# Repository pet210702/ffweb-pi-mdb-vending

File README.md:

# FF Getränkeautomat – MDB- & FFWEB-Steuerung für den SandenVendo G-Drink DM9

Open-Source-Steuerung auf Basis eines Raspberry Pi, die einen **SandenVendo G-Drink DM9** (über den **MDB-Cashless-Bus**), einen **13,56-MHz-USB-RFID-Leser**, ein **0,96"-I2C-OLED-Display**, **3 Bedientasten** und **FFWEB (`https://www.ffweb.at`)** zur Getränkeverrechnung im Feuerwehrhaus miteinander verbindet.

Läuft zuverlässig selbst auf einem einkernigen **Raspberry Pi 1 Model B+ (ARMv6, 512 MB RAM)** sowie auf neueren Modellen (Pi Zero 2 W, Pi 3, Pi 4, Pi 5).

---

## ✨ Funktionen

- **Zwei Bedienabläufe – „Chip zuerst“ und „Getränk zuerst“:**
  - *Chip zuerst:* Feuerwehr-Chip vorhalten → zwischen privatem Guthaben oder einer offenen Verrechnungsliste wählen → Kredit wird am G-Drink DM9 freigegeben → Getränk am Automaten wählen.
  - *Getränk zuerst:* Fach am G-Drink DM9 wählen → das OLED zeigt `Chip vorhalten` mit Getränkename und Preis → Chip vorhalten, die Ausgabe erfolgt sofort.
- **Verrechnungslisten / Anlässe:**
  - Offene Listen für Einsätze, Übungen oder Kameradschaftsabende / Sitzungen direkt im Web-Dashboard anlegen.
  - Sind Listen offen, wählen Mitglieder mit den **3 Tasten** (`Zurück`, `OK`, `Weiter`) zwischen **Privat (Guthaben)** und einer aktiven **Verrechnungsliste** (`0,00 EUR` privat, Buchung auf den Anlass).
- **Sichere Abrechnung – kein Abzug bei Störung oder Abbruch:**
  - Durchgehend Ganzzahl-Arithmetik in Cent.
  - Abgebucht wird **erst**, wenn der optische Ausgabesensor des DM9 `c,VEND,SUCCESS` meldet. Steckengebliebene Flaschen (`c,ERR,VEND 3`) oder abgebrochene Auswahlen (`c,ERR,VEND 1`) kosten `0,00 EUR`.
- **Offline-fähige SQLite-Warteschlange & idempotente FFWEB-Synchronisation:**
  - Jeder Verkauf wird sofort lokal in SQLite (`WAL`-Modus) mit eindeutigem `idempotency_key` (UUID) gespeichert.
  - Ist das WLAN/LAN oder FFWEB vorübergehend nicht erreichbar, überträgt ein Hintergrunddienst offene Buchungen automatisch nach – ohne Doppelbuchungen.
- **0,96"-OLED-Statusanzeige & Hardware-Überwachung:**
  - 4-zeilige Anzeige (`SSD1306` / `SH1106`, `128×64`) mit Bildschirmschoner, Boot-Splash und automatischer Textanpassung.
  - **OLED-Hot-Plug:** Wird das Display kurz getrennt oder verliert es die Versorgung, verbindet es sich automatisch neu und wird ohne Flackern neu initialisiert.
  - **RFID-Überwachung:** Wird der USB-Leser abgesteckt, erscheint sofort `FEHLER: RFID / Lesegerät getrennt / USB prüfen!`; nach dem Wiederanstecken läuft alles innerhalb von ca. 1,5 s weiter.
  - **Diagnose-Kombination (Taste 1 + 3):** Gleichzeitiges Drücken der linken und rechten Taste zeigt 10 Sekunden lang LAN-IP, MDB-Status, RFID-Status und die Anzahl offener Synchronisationen.
- **Web-Dashboard & virtueller G-Drink-DM9-Simulator (`/`):**
  - Fachbelegung, Test-Chips und Verrechnungslisten verwalten sowie den Live-Zustand der Hardware per Server-Sent Events (SSE) verfolgen.
  - Vollständiger Browser-Simulator für DM9, RFID-Leser, 3 Tasten und einen 128×64-OLED-Spiegel – alles lässt sich testen, bevor echte MDB-Hardware angeschlossen ist.

---

## 🛒 Stückliste

| Komponente | Empfohlenes Modell / Spezifikation | Schnittstelle | Hinweise |
| :--- | :--- | :--- | :--- |
| **Einplatinenrechner** | Raspberry Pi 1 Model B+ Rev 1.2 (oder Pi 3B+ / 4B / Zero 2 W) | Ethernet / USB / 40-Pin-GPIO | Debian Trixie / Raspberry Pi OS (32 oder 64 Bit) |
| **Kühlung (empfohlen beim Pi 1)** | 5-V-Alu-Kühlkörper + Lüfter + Kupfer-Shim (`15×15 mm`) | 5 V & GND (GPIO) | Ermöglicht stabilen 1000-MHz-Turbo bei ca. 30 °C |
| **MDB-Cashless-Interface** | **Qibixx MDB-USB Interface** (oder Qibixx MDB Pi HAT) | USB-CDC seriell (`/dev/ttyACM0`) | Verbindet den Pi mit dem 6-poligen Molex-MDB-Bus des Automaten |
| **RFID-Leser** | **13,56-MHz-USB-HID-Leser** (z. B. `Sycreader` / `IC_Reader 08ff:0009`) | USB-HID (`evdev`) | Liefert eine 10-stellige dezimale UID von MIFARE-Classic-/NFC-Chips |
| **OLED-Display** | **0,96"-I2C-OLED (`128×64`)** (`SSD1306` oder `SH1106`) | I2C (`/dev/i2c-1`, `0x3C`) | 4-polig (`VCC`, `GND`, `SCL`, `SDA`) |
| **Bedientasten (3×)** | Taster (6-mm-Printtaster oder 12/16-mm-Einbautaster) | GPIO + GND (Active-Low) | Nutzt die internen Pull-ups des Pi – keine externen Widerstände nötig |
| **Frontplatine (optional)** | [Eigene Frontplatine](#-frontplatine-oled--3-tasten) mit OLED + 3 Tastern | 7-polig JST-XH / Stiftleiste | Siehe [`hardware/front_panel_pcb`](hardware/front_panel_pcb/) |
| **Netzteil & Speicher** | Offizielles 5-V-Netzteil + 16-GB-Industrie-microSD | Strom / SD | High-Endurance-microSD für Dauerbetrieb empfohlen |
| **Getränkeautomat** | **SandenVendo G-Drink DM9** (mit SF01-Steuerplatine) | MDB-Slave | Lift-Automat für Flaschen/Dosen |

---

## 🔌 Verdrahtung (40-Pin-GPIO-Leiste des Raspberry Pi)

Alle Komponenten werden direkt an die GPIO-Leiste angeschlossen – ein zusätzlicher HAT ist nicht nötig:

```text
                 Raspberry Pi 40-Pin-GPIO-Leiste (Pins 1–20)
                 ┌──────────────────────┬──────────────────────┐
   OLED VCC  <── │ (01) 3,3 V           │ (02) 5 V             │──> Lüfter + (rot)
   OLED SDA  <── │ (03) GPIO 2 (SDA1)   │ (04) 5 V             │
   OLED SCL  <── │ (05) GPIO 3 (SCL1)   │ (06) GND             │──> Lüfter – (schwarz)
                 │ (07) GPIO 4          │ (08) GPIO 14 (TXD)   │
   OLED GND  <── │ (09) GND             │ (10) GPIO 15 (RXD)   │
   Taste 1   <── │ (11) GPIO 17         │ (12) GPIO 18         │
   Taste 2   <── │ (13) GPIO 27         │ (14) GND             │──> GND Taste 1 & 2
   Taste 3   <── │ (15) GPIO 22         │ (16) GPIO 23         │
                 │ (17) 3,3 V           │ (18) GPIO 24         │
                 │ (19) GPIO 10 (MOSI)  │ (20) GND             │──> GND Taste 3
                 └──────────────────────┴──────────────────────┘
```

### 1. 0,96"-I2C-OLED (`SSD1306` @ `0x3C`)
| OLED-Pin | Physischer Pin am Pi | GPIO / Funktion |
| :--- | :--- | :--- |
| **VCC** | **Pin 1** | `3,3 V` |
| **GND** | **Pin 9** | `GND` |
| **SDA** | **Pin 3** | `GPIO 2 (I2C1 SDA)` |
| **SCL** | **Pin 5** | `GPIO 3 (I2C1 SCL)` |

### 2. Drei Bedientasten (Active-Low mit internem Pull-up)
Jeder Taster hat zwei Anschlüsse: einer an den **GPIO-Pin**, der andere an einen beliebigen **GND-Pin** (Pins `14` und `20` liegen direkt gegenüber; alternativ eine gemeinsame Masseleitung durchschleifen).

| Position | Funktion | GPIO (BCM) | Physischer Pin | GND-Pin |
| :--- | :--- | :--- | :--- | :--- |
| **Taste 1 (links)** | **Zurück / Abbruch** | `GPIO 17` | **Pin 11** | **Pin 14** |
| **Taste 2 (Mitte)** | **Auswahl / OK** | `GPIO 27` | **Pin 13** | **Pin 14** |
| **Taste 3 (rechts)** | **Weiter ▶** | `GPIO 22` | **Pin 15** | **Pin 20** |

> **Tipp:** Im Ruhezustand (`IDLE`) **Taste 1 + Taste 3** gleichzeitig drücken, um das **10-Sekunden-Diagnosemenü** auf dem OLED anzuzeigen.

### 3. 5-V-Lüfter
| Lüfterkabel | Physischer Pin am Pi | Funktion |
| :--- | :--- | :--- |
| **Rot (+5 V)** | **Pin 2** oder **Pin 4** | `5 V` |
| **Schwarz (GND)** | **Pin 6** | `GND` |

### 4. USB-Geräte
- **USB-Port 1:** 13,56-MHz-USB-HID-RFID-Leser (`/dev/input/by-id/usb-...-event-kbd`).
- **USB-Port 2:** Qibixx MDB-USB Interface (`/dev/ttyACM0`), über den MDB-Kabelbaum mit dem G-Drink DM9 verbunden.

---

## 🟩 Frontplatine (OLED + 3 Tasten)

Für einen sauberen Einbau in die Automatentür gibt es eine eigene 2-lagige Frontplatine (`60 × 56 mm`, KiCad 9):

- **Vorderseite:** nur das 0,96"-OLED und die 3 Taster (`Zurück`, `OK`, `Weiter`) – keine sichtbaren Kabel.
- **Rückseite:** 7-poliger JST-XH-Stecker (`J1`) bzw. alternativ 7-polige 2,54-mm-Stiftleiste (`J2`) sowie der 100-nF-Abblockkondensator.
- Die 7 Signale (`+3V3`, `SDA`, `SCL`, `GND`, 3× Taster) passen direkt auf die Pins 1–15 der linken Reihe der GPIO-Leiste – exakt nach der Belegung oben.
- Fertige Gerber-Daten, BOM, Bestückungsdaten (JLCPCB) und ein STEP-Modell liegen in [`hardware/front_panel_pcb/production/`](hardware/front_panel_pcb/production/).

Details zu Pinbelegung, Abmessungen und Stückliste: [`hardware/front_panel_pcb/README.md`](hardware/front_panel_pcb/README.md).

---

## ⚙️ Hinweis zum RFID-UID-Format (USB-Leser vs. Smartphone-App)

Normale 13,56-MHz-MIFARE-Classic-Chips haben eine 4 Byte lange Seriennummer.
- **Smartphone-Apps (z. B. NFC Tools):** zeigen die Bytes in MSB-Reihenfolge (`04:A2:F3:9B`).
- **USB-Leser (10-stellige Dezimalausgabe):** drehen die 4 Bytes um (LSB zuerst: `9B F3 A2 04`) und geben den 32-Bit-Wert als 10-stellige Dezimalzahl mit führenden Nullen aus (`2616435204`).
- Mit dem **Live-Chip-Scanner** im Web-Dashboard (`http://<pi-ip>:8000`) sieht man die exakte UID des USB-Lesers und kann sie mit einem Klick kopieren.

---

## 🚀 Schnellstart (lokale Entwicklung & Simulator unter macOS / Linux)

Das komplette System läuft auch ohne angeschlossene Hardware mit dem eingebauten Simulator:

```bash
git clone https://github.com/pet210702/ffweb-pi-mdb-vending.git
cd ffweb-pi-mdb-vending

python3 -m venv .venv
source .venv/bin/activate
pip install -r requirements.txt

# Automatische Tests ausführen
pytest -v

# FastAPI-Server + virtuellen G-Drink DM9 starten
uvicorn app.main:app --reload --port 8000
```

- **Web-Dashboard & Simulator:** `http://localhost:8000`
- **Interaktive API-Dokumentation (OpenAPI):** `http://localhost:8000/docs`

---

## 🍓 Installation auf dem Raspberry Pi

### Schritt 1: Projekt kopieren & Installer ausführen
Das Repository vom Arbeitsrechner auf den Pi kopieren und [`deploy/install_pi.sh`](deploy/install_pi.sh) starten:

```bash
scp -r . ffadmin@<pi-ip>:~/getraenkeautomat
ssh ffadmin@<pi-ip> "bash ~/getraenkeautomat/deploy/install_pi.sh"
```

Was [`deploy/install_pi.sh`](deploy/install_pi.sh) automatisch erledigt:
1. Installiert vorkompilierte Debian-/Raspberry-Pi-OS-Pakete (`python3-fastapi`, `python3-uvicorn`, `python3-httpx`, `python3-serial`, `python3-evdev`, `python3-luma.oled`, `python3-gpiod`, `i2c-tools`, `fonts-dejavu-core`) – dadurch ist die Installation auch auf 32-Bit-ARMv6 in Sekunden erledigt.
2. Aktiviert den I2C-Bus (`/dev/i2c-1`) und fügt den Benutzer den Gruppen `input`, `dialout`, `i2c` und `gpio` hinzu.
3. Installiert die Anwendung nach `/opt/getraenkeautomat` und legt `/opt/getraenkeautomat/.env` aus `.env.example` an.
4. Richtet zwei `systemd`-Dienste ein und aktiviert sie:
   - `getraenkeautomat-boot-oled.service`: zeigt sofort einen Boot-Splash am OLED, sobald `/dev/i2c-1` verfügbar ist.
   - `getraenkeautomat.service`: startet die FastAPI-/Uvicorn-Steuerung mit automatischem Neustart.

### Schritt 2 (optional): Schnellstart & Übertaktung für den Raspberry Pi 1
Auf einem **Raspberry Pi 1 Model B+** mit aktiver Kühlung deaktiviert [`deploy/optimize_pi.sh`](deploy/optimize_pi.sh) nicht benötigte Dienste (`cloud-init`, `bluetooth`, `wpa_supplicant`, `NetworkManager-wait-online`) und aktiviert das offizielle 1000-MHz-Turbo-Profil:

```bash
ssh ffadmin@<pi-ip> "bash /opt/getraenkeautomat/deploy/optimize_pi.sh && sudo reboot"
```

---

## 🔄 Vom Simulator auf echte MDB-Hardware & FFWEB umstellen

`/opt/getraenkeautomat/.env` auf dem Pi bearbeiten und den Dienst neu starten (`sudo systemctl restart getraenkeautomat`):

### 1. Qibixx MDB-USB Interface aktivieren
```ini
MDB_MODE=qibixx
MDB_SERIAL_PORT=/dev/ttyACM0
MDB_BAUDRATE=115200
```
*Auf der SF01-Steuerplatine des G-Drink DM9 muss das Protokoll auf **MDB** eingestellt und die bargeldlose Zahlung unter `PAYMENT SETTING` aktiviert sein.*

### 2. Live-Anbindung an FFWEB aktivieren
```ini
FFWEB_MODE=http
FFWEB_BASE_URL=https://api.ffweb.at
FFWEB_API_KEY=dein_api_token_der_wache
FFWEB_MEMBER_LOOKUP_PATH=/api/v1/vending/members/{chip_uid}
FFWEB_PRODUCTS_PATH=/api/v1/vending/products
FFWEB_VEND_PATH=/api/v1/vending/consumptions
```

### 3. Übersicht aller `.env`-Einstellungen

| Variable | Standard | Beschreibung |
| :--- | :--- | :--- |
| `HOST` / `PORT` | `0.0.0.0` / `8000` | Adresse und Port des HTTP-Servers |
| `DB_PATH` | `data/vending.db` | Pfad der lokalen SQLite-Datenbank (WAL-Modus) |
| `ADMIN_API_TOKEN` | *(leer)* | Optionaler `X-Admin-Token` / Bearer-Token für schreibende Admin-Routen |
| `MDB_MODE` | `simulator` | `simulator` (virtueller DM9) oder `qibixx` (echte serielle MDB-Hardware) |
| `MDB_SERIAL_PORT` | `/dev/ttyACM0` | Serielles Gerät des Qibixx MDB-USB / Pi HAT |
| `MDB_BAUDRATE` | `115200` | Baudrate der seriellen MDB-Schnittstelle |
| `RFID_MODE` | `auto` | `auto` (Linux-`evdev`, falls vorhanden), `evdev` oder `simulator` |
| `RFID_DEVICE_PATH` | *(leer)* | Optional expliziter Pfad `/dev/input/by-id/...` (sonst automatische Erkennung) |
| `OLED_MODE` | `auto` | `auto` (`ssd1306` an `/dev/i2c-1`), `ssd1306`, `sh1106` oder `disabled` |
| `OLED_I2C_PORT` | `1` | I2C-Bus-Nummer |
| `OLED_I2C_ADDRESS` | `0x3C` | I2C-Adresse des OLED-Displays |
| `OLED_SCREENSAVER_SEC` | `90` | Sekunden ohne Aktivität bis zum Abschalten des OLED |
| `OLED_STARTUP_DIAG_SEC` | `6` | Anzeigedauer der Diagnose nach dem Start |
| `BUTTONS_MODE` | `auto` | `auto` (`/dev/gpiochip0` über `libgpiod` v2), `simulator` oder `disabled` |
| `BUTTONS_CHIP_PATH` | `/dev/gpiochip0` | GPIO-Chip für die Tasten |
| `BUTTON_PIN_BACK` | `17` | BCM-GPIO für Taste 1 (links: Zurück / Abbruch) |
| `BUTTON_PIN_SELECT` | `27` | BCM-GPIO für Taste 2 (Mitte: Auswahl / OK) |
| `BUTTON_PIN_NEXT` | `22` | BCM-GPIO für Taste 3 (rechts: Weiter) |
| `BUTTON_DEBOUNCE_MS` | `50` | Entprellzeit der Tasten in Millisekunden |
| `BILLING_SELECTION_TIMEOUT_SEC` | `12` | Sekunden, bis die Auswahl Privat/Verrechnungsliste abläuft |
| `SESSION_TIMEOUT_SEC` | `30` | Sekunden, die ein freigegebener MDB-Kredit am DM9 offen bleibt |
| `AWAITING_CHIP_TIMEOUT_SEC` | `15` | Sekunden, die bei „Getränk zuerst“ auf einen Chip gewartet wird |
| `DISPENSE_TIMEOUT_SEC` | `25` | Maximale Wartezeit auf die Bestätigung des Ausgabesensors |
| `ALLOW_UNMAPPED_SLOTS` | `false` | Ob nicht zugeordnete Fächer zum Automatenpreis verkauft werden dürfen |
| `FFWEB_MODE` | `mock` | `mock` (lokale Mitglieder/Guthaben in SQLite) oder `http` (echte FFWEB-REST-API) |
| `FFWEB_TIMEOUT_SEC` | `4.0` | Timeout für FFWEB-Anfragen in Sekunden |
| `SYNC_RETRY_INTERVAL_SEC` | `10` | Intervall für erneute Synchronisationsversuche |

---

## 🗂️ Projektstruktur

```text
.
├── app/
│   ├── api/routes.py          # FastAPI-REST-Endpunkte & SSE-Echtzeitstream
│   ├── buttons/               # GPIO-Treiber für die 3 Tasten (libgpiod v2 + Kombinationserkennung)
│   ├── ffweb/                 # Mock- & HTTP-FFWEB-Client + robuster Synchronisationsdienst
│   ├── mdb/                   # Qibixx-MDB-Cashless-Treiber & virtueller G-Drink-DM9-Simulator
│   ├── oled/                  # SSD1306/SH1106-OLED-Ansteuerung (128×64) & Boot-Splash
│   ├── rfid/                  # evdev-USB-HID-Leser mit Hot-Plug- & Trennungserkennung
│   ├── static/index.html      # Admin-Dashboard & virtueller Hardware-Simulator
│   ├── config.py              # Laden der Konfiguration aus Umgebungsvariablen
│   ├── db.py                  # SQLite-WAL-Speicher (Fächer, Mitglieder, Listen, Verkaufsprotokoll)
│   ├── events.py              # Asynchroner Pub/Sub-Eventbus
│   ├── main.py                # FastAPI-Lebenszyklus & Verdrahtung der Dienste
│   └── state_machine.py       # Zentrale Zustandsmaschine (Chip zuerst, Getränk zuerst, Listen)
├── deploy/
│   ├── getraenkeautomat-boot-oled.service  # systemd-Unit für den OLED-Boot-Splash
│   ├── getraenkeautomat.service            # systemd-Unit der Hauptsteuerung
│   ├── install_pi.sh                       # Installer für den Raspberry Pi
│   └── optimize_pi.sh                      # Schnellstart- & 1000-MHz-Skript für den Pi 1
├── hardware/
│   └── front_panel_pcb/       # KiCad-Projekt der Frontplatine (OLED + 3 Taster) inkl. Fertigungsdaten
├── tests/                     # pytest-Tests (Verkaufsabläufe, Listen, Hardware-Sonderfälle)
├── .env.example               # Beispielkonfiguration
├── pyproject.toml             # Projekt- & pytest-Einstellungen
└── requirements.txt           # Python-Abhängigkeiten
```

---

## 📄 Lizenz

Veröffentlicht unter der [MIT-Lizenz](LICENSE).

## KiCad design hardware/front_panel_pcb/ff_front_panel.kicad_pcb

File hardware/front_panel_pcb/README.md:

# FF Getränkeautomat – Frontplatine (0,96"-I2C-OLED + 3× 6-mm-Taster)

Eigenständige 2-lagige Frontplatine (`60,0 mm × 56,0 mm`), entworfen in **KiCad 9.0** für die Raspberry-Pi-Steuerung des **FF Getränkeautomaten**.

- **Saubere Vorderseite (`F.Cu`):** Auf der für Benutzer sichtbaren Seite sitzen nur das **0,96"-I2C-OLED (`128×64`, `VCC – GND – SCL – SDA`)**, direkt in `J3` eingelötet (abgestützt mit `2,5 mm` M2-Abstandshaltern auf `H5`–`H8`), und die **3× `6×6 mm` THT-Taster (`Zurück`, `OK`, `Weiter`)**.
- **Verdeckte Verkabelung auf der Rückseite (`B.Cu`):** Der **7-polige JST-XH-Stecker (`2,50 mm`, `J1`)**, die **7-polige `2,54 mm` Stiftleiste (`J2`)** und der **`100 nF` Abblockkondensator (`C1`)** sind auf der **Rückseite (`B.Cu`)** bestückt. Dadurch laufen alle Kabel hinter der Platine in den Automaten – von vorne ist kein Kabel sichtbar.

---

## 📐 Technische Daten

| Parameter | Wert |
| :--- | :--- |
| **Abmessungen** | `60,0 mm × 56,0 mm` (Ecken mit `R3,0 mm` abgerundet) |
| **Lagen** | 2 Lagen FR-4 (`F.Cu` & `B.Cu`), vollflächige `GND`-Kupferflächen auf beiden Lagen |
| **Dicke / Kupfer** | `1,6 mm` Standard-FR-4, `1 oz` (`35 µm`) Kupfer |
| **Befestigungslöcher (Ecken)** | 4× `M3` (`Ø 3,2 mm`, nicht durchkontaktiert, `H1`–`H4`) im Raster `52,0 mm × 48,0 mm` |
| **Löcher für OLED-Abstandshalter** | 4× `M2` (`Ø 2,2 mm`, nicht durchkontaktiert, `H5`–`H8`) im Raster `23,0 mm × 23,5 mm` (`2,5 mm` Abstandshalter) |
| **Tasterabstand** | `16,0 mm` Mittenabstand horizontal (`X = 14,0 / 30,0 / 46,0 mm` vom linken Rand) |
| **Leiterbahnen** | `0,50 mm` Versorgung (`+3V3`), `0,35 mm` Signale (`I2C`, Taster), `0,30 mm` Abstand zu Kupferflächen |
| **ERC / DRC** | **0 ERC-Fehler / 0 DRC-Fehler / 0 offene Verbindungen** (geprüft mit `kicad-cli 9.0.7`) |

---

## 🔌 Belegung der Steckverbinder (`J1` & `J2` auf `B.Cu`) & Anschluss an den Raspberry Pi

`J1` (7-polig JST-XH, Rückseite unten) und `J2` (7-polige `2,54 mm` Stiftleiste, Rückseite seitlich) sitzen beide auf der **Rückseite (`B.Cu`)** und sind parallel verdrahtet – es muss nur einer von beiden bestückt werden.

Alle 7 Signale liegen auf der **linken Reihe (ungerade Pins)** der 40-poligen GPIO-Leiste des Raspberry Pi:

| Pin `J1` / `J2` | Netz | Funktion | Physischer Pin am Pi | BCM-GPIO |
| :---: | :--- | :--- | :---: | :--- |
| **Pin 1** *(eckiges Pad)* | `+3V3` | `3,3 V` Versorgung für das OLED | **Pin 1** | `3,3 V` |
| **Pin 2** | `I2C_SDA` | OLED I2C-Daten | **Pin 3** | `GPIO 2 (SDA1)` |
| **Pin 3** | `I2C_SCL` | OLED I2C-Takt | **Pin 5** | `GPIO 3 (SCL1)` |
| **Pin 4** | `GND` | Gemeinsame Masse (OLED & Taster) | **Pin 9** *(oder 14 / 20)* | `GND` |
| **Pin 5** | `BTN1_BACK` | Taste 1 links (`◀ Zurück / Abbruch`) | **Pin 11** | `GPIO 17` *(Active-Low)* |
| **Pin 6** | `BTN2_OK` | Taste 2 Mitte (`● Auswahl / OK`) | **Pin 13** | `GPIO 27` *(Active-Low)* |
| **Pin 7** | `BTN3_NEXT` | Taste 3 rechts (`Weiter ▶`) | **Pin 15** | `GPIO 22` *(Active-Low)* |

### 4-poliger OLED-Anschluss zum Direkteinlöten (`J3`, Vorderseite `F.Cu`)
Die 4 Stiftkontakte des 0,96"-I2C-OLED (`VCC – GND – SCL – SDA`, von links nach rechts mit Blick auf die Vorderseite) von vorne direkt in `J3` stecken und auf der Rückseite verlöten. Die beiden unteren M2-Löcher (`H7` & `H8`) mit **`2,5 mm` (oder `3 mm`) M2-Nylon-Abstandshaltern** bestücken:
- **Pin 1 (eckiges Pad, links):** `VCC` (`+3V3`)
- **Pin 2:** `GND`
- **Pin 3:** `SCL` (`I2C_SCL`)
- **Pin 4 (rechts):** `SDA` (`I2C_SDA`)

---

## 🛒 Stückliste (BOM)

| Ref | Seite | Anz. | Wert / Beschreibung | Gehäuse / Footprint | Hinweise |
| :--- | :---: | :---: | :--- | :--- | :--- |
| **`J3`** | **Vorne (`F.Cu`)** | 1 | `0,96"` I2C-OLED (`128×64`, 4-polig `2,54 mm`) | `PinHeader_1x04_P2.54mm_Vertical` | Die 4 Stifte des OLED (`VCC-GND-SCL-SDA`) direkt in `J3` löten + `2,5 mm` M2-Abstandshalter |
| **`SW1`–`SW3`** | **Vorne (`F.Cu`)** | 3 | `6×6 mm` THT-Taster (`H = 5 mm` oder `7 mm`) | `SW_PUSH_6mm` | Standard-Printtaster `6×6 mm` mit 4 Beinen (passend zur Höhe des OLED) |
| **`C1`** | **Hinten (`B.Cu`)** | 1 | `100 nF` (`0,1 µF`) Keramik-Scheibenkondensator | `C_Disc_D4.7mm_W2.5mm_P5.00mm` | Auf der Rückseite, damit die Vorderseite frei bleibt |
| **`J1`** | **Hinten (`B.Cu`)** | 1 | 7-polige JST-XH-Stiftleiste (`B7B-XH-A`, `2,50 mm`) | `JST_XH_B7B-XH-A_1x07_P2.50mm_Vertical` | Auf der Rückseite für verdeckte Kabelführung |
| **`J2`** | **Hinten (`B.Cu`)** | 1 | `1×7` Stiftleiste (`2,54 mm` Raster) | `PinHeader_1x07_P2.54mm_Vertical` | Auf der Rückseite; optionale Alternative zu `J1` |
| **`H1`–`H4`** | Durchgehend | 4 | `M3` Befestigungslöcher (`Ø 3,2 mm`) | `MountingHole_3.2mm_M3` | Befestigung im Gehäuse (Abstand `52 × 48 mm`) |
| **`H5`–`H8`** | Durchgehend | 4 | `M2` Löcher für Abstandshalter (`Ø 2,2 mm`) | `MountingHole_2.2mm_M2` | Für `2,5 mm` `M2`-Abstandshalter unter dem 0,96"-OLED |

---

## 🏭 Fertigungsdaten

Alle Dateien für die Fertigung liegen in [`production/`](production/):
- **[`production/ff_front_panel_gerbers.zip`](production/ff_front_panel_gerbers.zip)**: Direkt bei **JLCPCB**, **PCBWay** oder **AISLER** hochladen (2 Lagen, `60 × 56 mm`, `1,6 mm` Dicke).
- **[`production/BOM.csv`](production/BOM.csv)** & **[`production/POS.csv`](production/POS.csv)**: Stückliste und Bestückungsdaten (Bauteilpositionen, Seite `F.Cu` / `B.Cu` jeweils korrekt angegeben).
- **[`production/JLCPCB_BOM.csv`](production/JLCPCB_BOM.csv)** & **[`production/JLCPCB_CPL.csv`](production/JLCPCB_CPL.csv)**: Stückliste und Bestückungsdaten im JLCPCB-Format.
- **[`production/ff_front_panel.step`](production/ff_front_panel.step)**: Vollständiges 3D-CAD-Modell (STEP).
- **[`docs/schematic.pdf`](docs/schematic.pdf)**: Schaltplan als druckbares A4-Vektor-PDF.

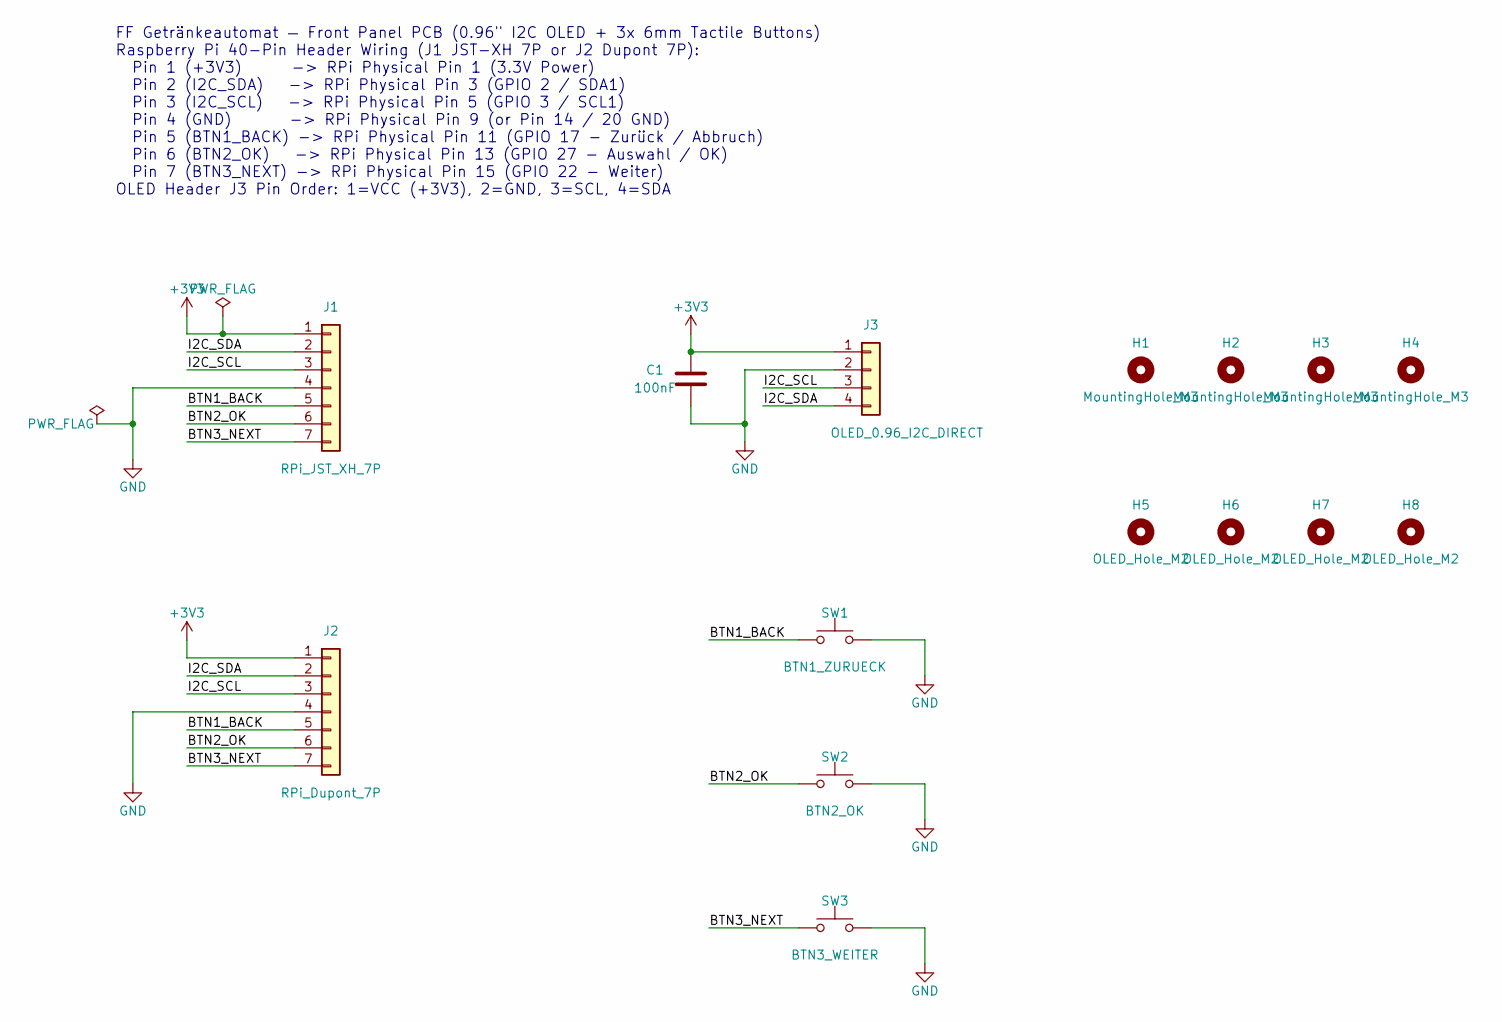
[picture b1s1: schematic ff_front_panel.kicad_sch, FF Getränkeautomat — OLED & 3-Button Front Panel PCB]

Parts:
C1: 100nF; C_Disc_D4.7mm_W2.5mm_P5.00mm
H1, H2, H3, H4: MountingHole_M3; MountingHole_3.2mm_M3
H5, H6, H7, H8: OLED_Hole_M2; MountingHole_2.2mm_M2
J1: RPi_JST_XH_7P; JST_XH_B7B-XH-A_1x07_P2.50mm_Vertical
J2: RPi_Dupont_7P; PinHeader_1x07_P2.54mm_Vertical
J3: OLED_0.96_I2C_DIRECT; PinHeader_1x04_P2.54mm_Vertical
SW1: BTN1_ZURUECK; SW_PUSH_6mm
SW2: BTN2_OK; SW_PUSH_6mm
SW3: BTN3_WEITER; SW_PUSH_6mm

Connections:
+3V3: C1.1, J1.1, J2.1, J3.1
/BTN1_BACK: J1.5, J2.5, SW1.1
/BTN2_OK: J1.6, J2.6, SW2.1
/BTN3_NEXT: J1.7, J2.7, SW3.1
/I2C_SCL: J1.3, J2.3, J3.3
/I2C_SDA: J1.2, J2.2, J3.4
GND: C1.2, J1.4, J2.4, J3.2, SW1.2, SW2.2, SW3.2

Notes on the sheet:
FF Getränkeautomat — Front Panel PCB (0.96" I2C OLED + 3x 6mm Tactile Buttons) Raspberry Pi 40-Pin Header Wiring (J1 JST-XH 7P or J2 Dupont 7P): Pin 1 (+3V3) -> RPi Physical Pin 1 (3.3V Power) Pin 2 (I2C_SDA) -> RPi Physical Pin 3 (GPIO 2 / SDA1) Pin 3 (I2C_SCL) -> RPi Physical Pin 5 (GPIO 3 / SCL1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

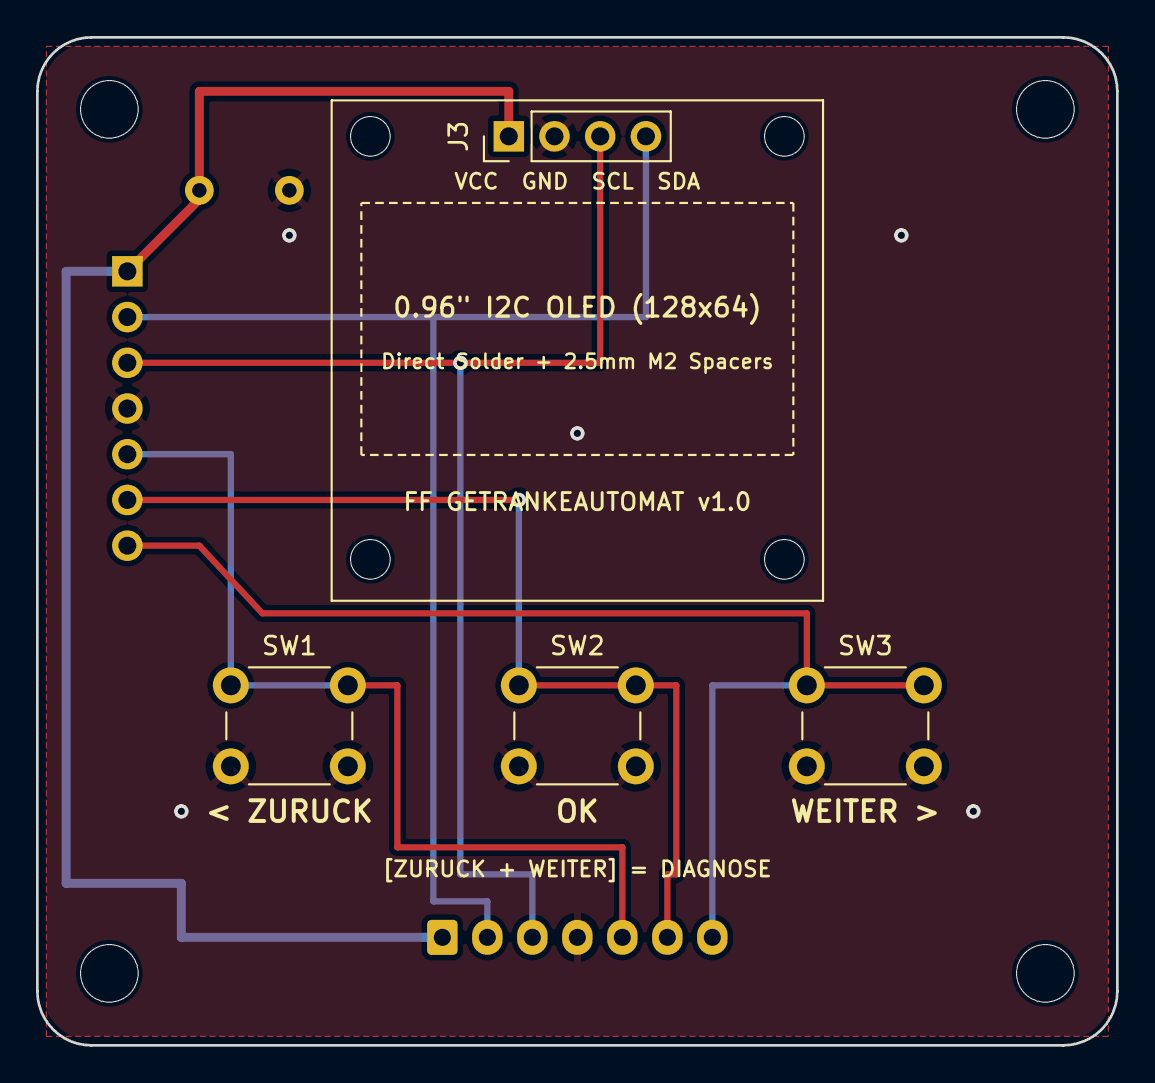
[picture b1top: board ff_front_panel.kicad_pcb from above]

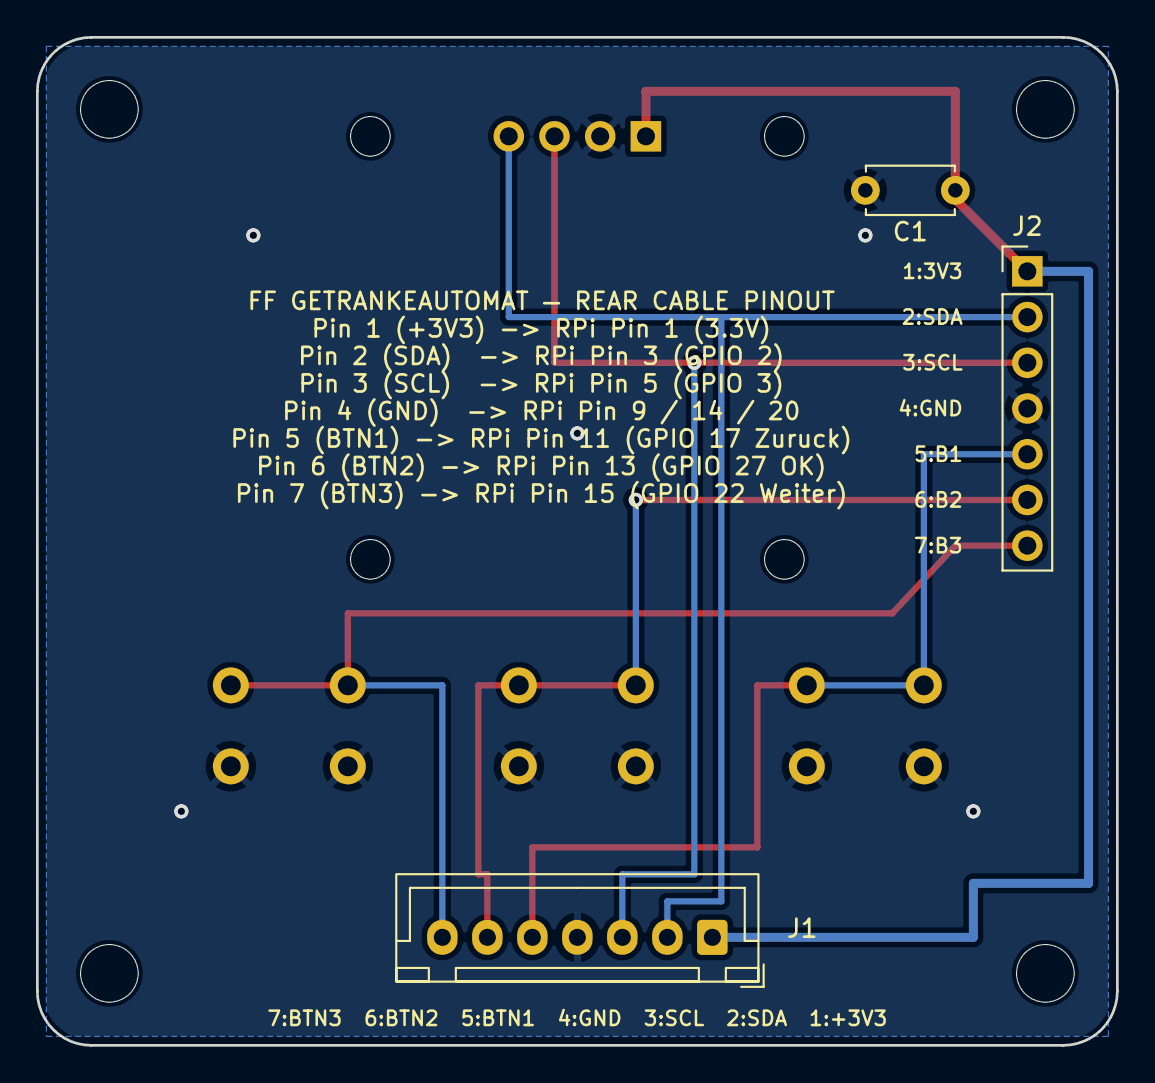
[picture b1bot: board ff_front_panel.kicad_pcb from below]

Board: 2 copper layers, 60.0 x 56.0 mm, 15 parts (3 on the bottom side), 7 nets.

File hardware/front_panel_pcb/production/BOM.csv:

"Refs","Value","Footprint","Qty","DNP"
"C1","100nF","Capacitor_THT:C_Disc_D4.7mm_W2.5mm_P5.00mm","1",""
"J1","RPi_JST_XH_7P","Connector_JST:JST_XH_B7B-XH-A_1x07_P2.50mm_Vertical","1",""
"J2","RPi_Dupont_7P","Connector_PinHeader_2.54mm:PinHeader_1x07_P2.54mm_Vertical","1",""
"J3","OLED_0.96_I2C_DIRECT","Connector_PinHeader_2.54mm:PinHeader_1x04_P2.54mm_Vertical","1",""
"SW1","BTN1_ZURUECK","Button_Switch_THT:SW_PUSH_6mm","1",""
"SW2","BTN2_OK","Button_Switch_THT:SW_PUSH_6mm","1",""
"SW3","BTN3_WEITER","Button_Switch_THT:SW_PUSH_6mm","1",""
